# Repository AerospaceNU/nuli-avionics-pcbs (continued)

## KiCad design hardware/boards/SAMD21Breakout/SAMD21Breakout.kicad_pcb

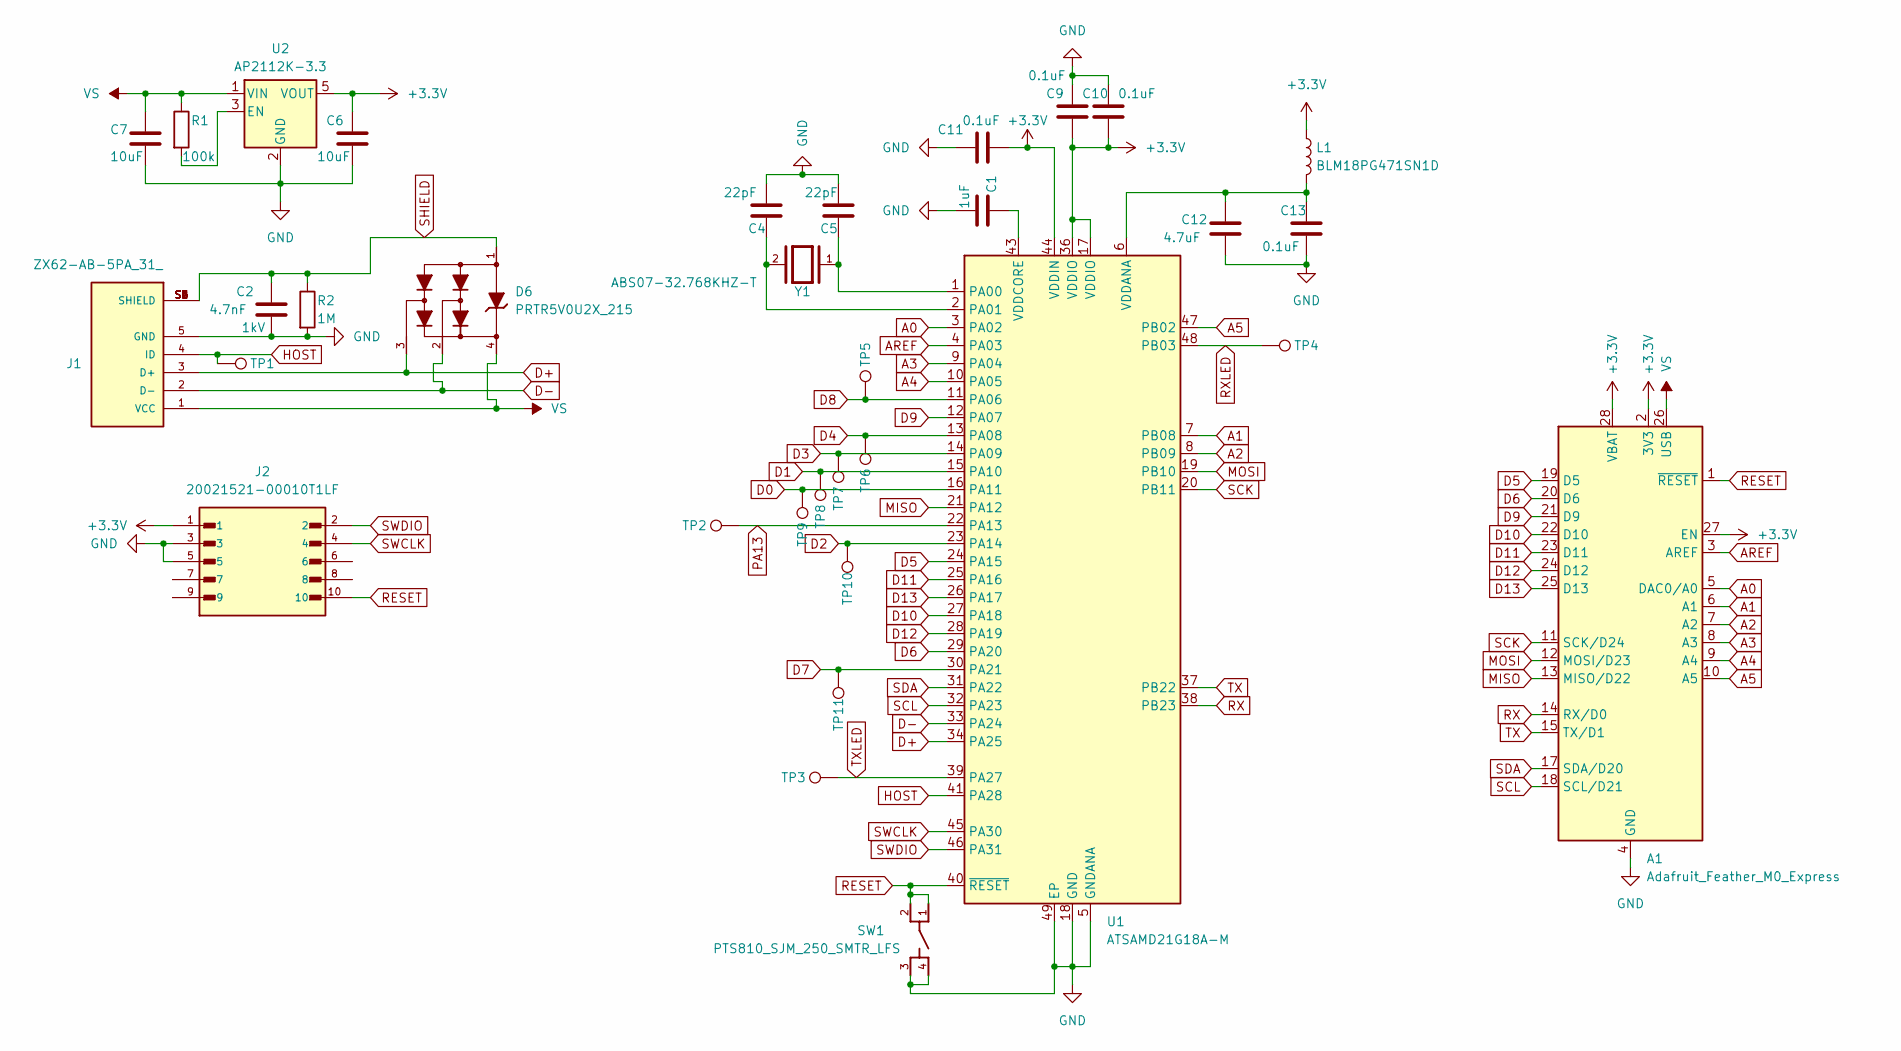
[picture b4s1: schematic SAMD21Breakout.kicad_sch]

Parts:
A1: Adafruit_Feather_M0_Express; Adafruit_Feather
C1: 1uF; C_0603_1608Metric
C2: 4.7nF; C_1206_3216Metric; Voltage 1kV
C4, C5: 22pF; C_0603_1608Metric
C6, C7: 10uF; C_0603_1608Metric
C9, C10, C11, C13: 0.1uF; C_0603_1608Metric
C12: 4.7uF; C_0603_1608Metric
D6: PRTR5V0U2X_215; SOT143B
J1: ZX62-AB-5PA_31_; HIROSE_ZX62-AB-5PA_31_; PARTREV Jan 1, 2022
J2: 20021521-00010T1LF; AMPHENOL_20021521-00010T1LF; PARTREV N
L1: BLM18PG471SN1D; L_0603_1608Metric
R1: 100k; R_0603_1608Metric
R2: 1M; R_0603_1608Metric
SW1: PTS810_SJM_250_SMTR_LFS; SW_PTS810_SJM_250_SMTR_LFS
TP1, TP2, TP3, TP4, TP5, TP6, TP7, TP8, TP9, TP10, TP11: TestPoint; TestPoint_Pad_D1.0mm
U1: ATSAMD21G18A-M; QFN-48-1EP_7x7mm_P0.5mm_EP5.15x5.15mm
U2: AP2112K-3.3; SOT-23-5
Y1: ABS07-32.768KHZ-T; XTAL_ABS07-32.768KHZ-T; PARTREV 08.19.15

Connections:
+3.3V: A1.2 (3V3), A1.27 (EN), A1.28 (VBAT), C6.1, C9.2, C10.2, C11.2, J2.1, L1.1, U1.17 (VDDIO), U1.36 (VDDIO), U1.44 (VDDIN), U2.5 (VOUT)
A0: A1.5 (DAC0/A0), U1.3 (PA02)
A1: A1.6 (A1), U1.7 (PB08)
A2: A1.7 (A2), U1.8 (PB09)
A3: A1.8 (A3), U1.9 (PA04)
A4: A1.9 (A4), U1.10 (PA05)
A5: A1.10 (A5), U1.47 (PB02)
AREF: A1.3 (AREF), U1.4 (PA03)
D0: TP9.1, U1.16 (PA11)
D1: TP8.1, U1.15 (PA10)
D2: TP10.1, U1.23 (PA14)
D3: TP7.1, U1.14 (PA09)
D4: TP6.1, U1.13 (PA08)
D5: A1.19 (D5), U1.24 (PA15)
D6: A1.20 (D6), U1.29 (PA20)
D7: TP11.1, U1.30 (PA21)
D8: TP5.1, U1.11 (PA06)
D9: A1.21 (D9), U1.12 (PA07)
D10: A1.22 (D10), U1.27 (PA18)
D11: A1.23 (D11), U1.25 (PA16)
D12: A1.24 (D12), U1.28 (PA19)
D13: A1.25 (D13), U1.26 (PA17)
D+: D6.3, J1.3 (D+), U1.34 (PA25)
D-: D6.2, J1.2 (D-), U1.33 (PA24)
GND: A1.4 (GND), A1.16 (GND), C1.2, C2.2, C4.2, C5.2, C6.2, C7.2, C9.1, C10.1, C11.1, C12.2, C13.2, J1.5 (GND), J2.3, J2.5, R2.2, SW1.3, SW1.4, U1.5 (GNDANA), U1.18 (GND), U1.35 (GND), U1.42 (GND), U1.49 (EP), U2.2 (GND)
HOST: J1.4 (ID), TP1.1, U1.41 (PA28)
MISO: A1.13 (MISO/D22), U1.21 (PA12)
MOSI: A1.12 (MOSI/D23), U1.19 (PB10)
unnamed: C5.1, U1.1 (PA00), Y1.1
unnamed: C4.1, U1.2 (PA01), Y1.2
unnamed: C12.1, C13.1, L1.2, U1.6 (VDDANA)
unnamed: C1.1, U1.43 (VDDCORE)
unnamed: R1.2, U2.3 (EN)
PA13: TP2.1, U1.22 (PA13)
RESET: A1.1 (~RESET), J2.10, SW1.1, SW1.2, U1.40 (~RESET)
RX: A1.14 (RX/D0), U1.38 (PB23)
RXLED: TP4.1, U1.48 (PB03)
SCK: A1.11 (SCK/D24), U1.20 (PB11)
SCL: A1.18 (SCL/D21), U1.32 (PA23)
SDA: A1.17 (SDA/D20), U1.31 (PA22)
SHIELD: C2.1, D6.1, J1.S1 (SHIELD), J1.S2 (SHIELD), J1.S3 (SHIELD), J1.S4 (SHIELD), J1.S5 (SHIELD), J1.S6 (SHIELD), R2.1
SWCLK: J2.4, U1.45 (PA30)
SWDIO: J2.2, U1.46 (PA31)
TX: A1.15 (TX/D1), U1.37 (PB22)
TXLED: TP3.1, U1.39 (PA27)
VS: A1.26 (USB), C7.1, D6.4, J1.1 (VCC), R1.1, U2.1 (VIN)

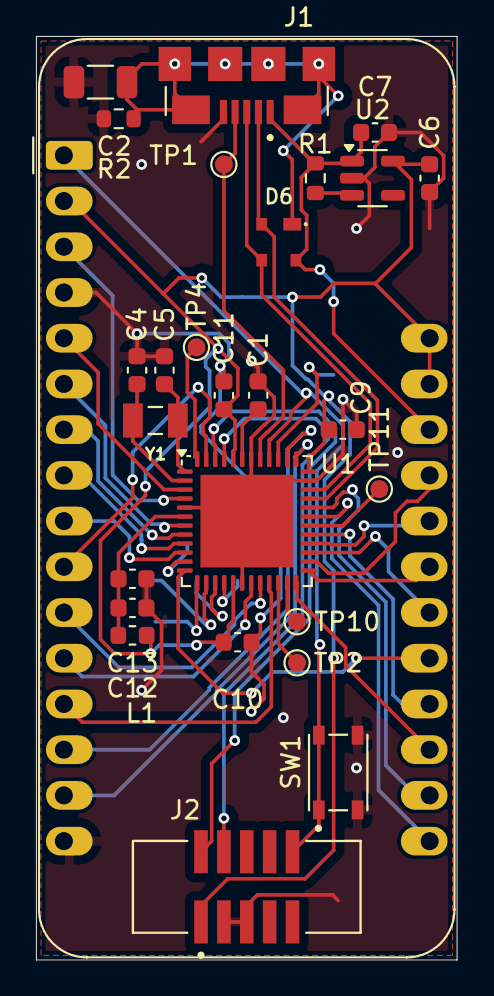
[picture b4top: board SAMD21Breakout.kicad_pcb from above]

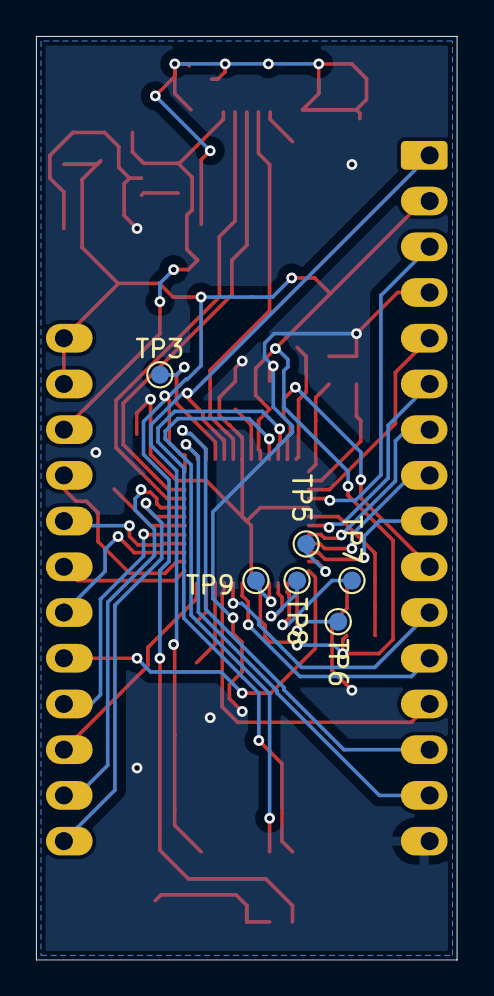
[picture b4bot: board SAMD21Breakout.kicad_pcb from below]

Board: 2 copper layers, 23.4 x 51.3 mm, 33 parts (6 on the bottom side), 46 nets.

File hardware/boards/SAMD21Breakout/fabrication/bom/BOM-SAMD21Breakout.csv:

Comment,Designator,Footprint,LCSC
PRTR5V0U2X_215,D6,SOT143B,C12333
ABS07-32.768KHZ-T,Y1,XTAL_ABS07-32.768KHZ-T,C130253
0.1uF,"C10,C11,C13,C9",C_0603_1608Metric,C14663
1uF,C1,C_0603_1608Metric,C15849
22pF,"C4,C5",C_0603_1608Metric,C1653
4.7uF,C12,C_0603_1608Metric,C19666
10uF,"C6,C7",C_0603_1608Metric,C19702
PTS810_SJM_250_SMTR_LFS,SW1,SW_PTS810_SJM_250_SMTR_LFS,C221895
1M,R2,R_0603_1608Metric,C22935
100k,R1,R_0603_1608Metric,C25803
ZX62-AB-5PA_31_,J1,HIROSE_ZX62-AB-5PA_31_,C2692071
20021521-00010T1LF,J2,AMPHENOL_20021521-00010T1LF,C2972785
AP2112K-3.3,U2,SOT-23-5,C51118
4.7nF,C2,C_1206_3216Metric,C9192
ATSAMD21G18A-M,U1,QFN-48-1EP_7x7mm_P0.5mm_EP5.15x5.15mm,C966903
BLM18PG471SN1D,L1,L_0603_1608Metric,C97853

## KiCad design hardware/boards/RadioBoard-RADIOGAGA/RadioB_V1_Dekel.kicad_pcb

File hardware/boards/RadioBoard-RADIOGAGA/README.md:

# RadioBoard-RADIOGAGA

RadioBoard by Itamar Dekel.

## Contributors

Riley Post, Itamar Dekel

## Status

**Version:** not recorded (the board's title block has no revision)
**Status:** Moved here from CADLab NULIAvionics/RadioBoard-RADIOGAGA; this folder is now the working copy.

## Description

RadioBoard by Itamar Dekel.

- KiCad project: `RadioB_V1_Dekel.kicad_pro`, last saved with KiCad 9.0
- Schematic sheets: `RadioB_V1_Dekel.kicad_sch`, `Connectors.kicad_sch`, `Power.kicad_sch`, `Pinouts.kicad_sch`, `RF Module.kicad_sch`, `untitled.kicad_sch`
- Board size: 60.0 x 22.1 mm
- `fabrication/`: `bom/`, `drill/`, `gerbers/`, `pick-and-place/`

## Manufacturing

- Layers: 6
- Thickness: 1.6 mm
- Surface finish: not set in the board stackup
- Minimum trace/space: 0.15 mm / 0.15 mm (smallest track on the board / default netclass clearance)
- Minimum drill: 0.25 mm (design rule)
- Manufacturer: JLCPCB (the fabrication outputs are JLCPCB's)

## Known Issues

None recorded.

## Revision History

| Version | Date | Changes |
|---|---|---|
| - | 2026-06-11 | Moved into this repo from CADLab NULIAvionics/RadioBoard-RADIOGAGA (history from 2026-04-21 to 2026-06-11 stays there) |

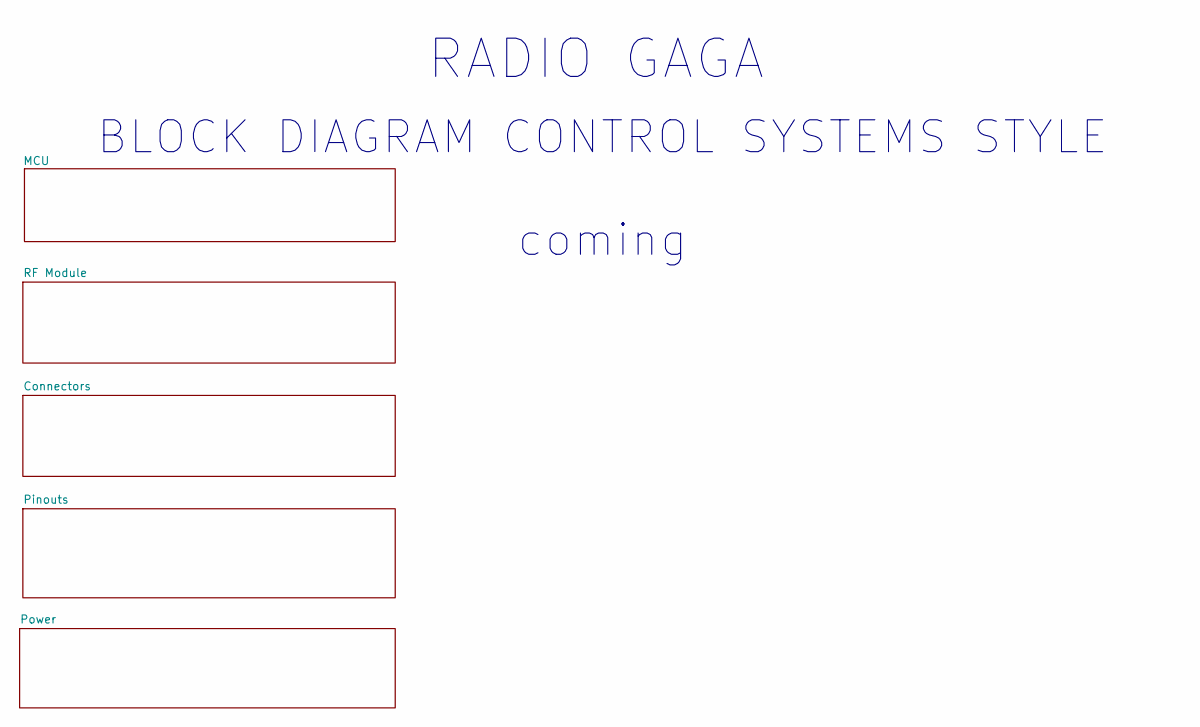
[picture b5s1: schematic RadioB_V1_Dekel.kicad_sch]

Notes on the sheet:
BLOCK DIAGRAM CONTROL SYSTEMS STYLE coming
RADIO GAGA

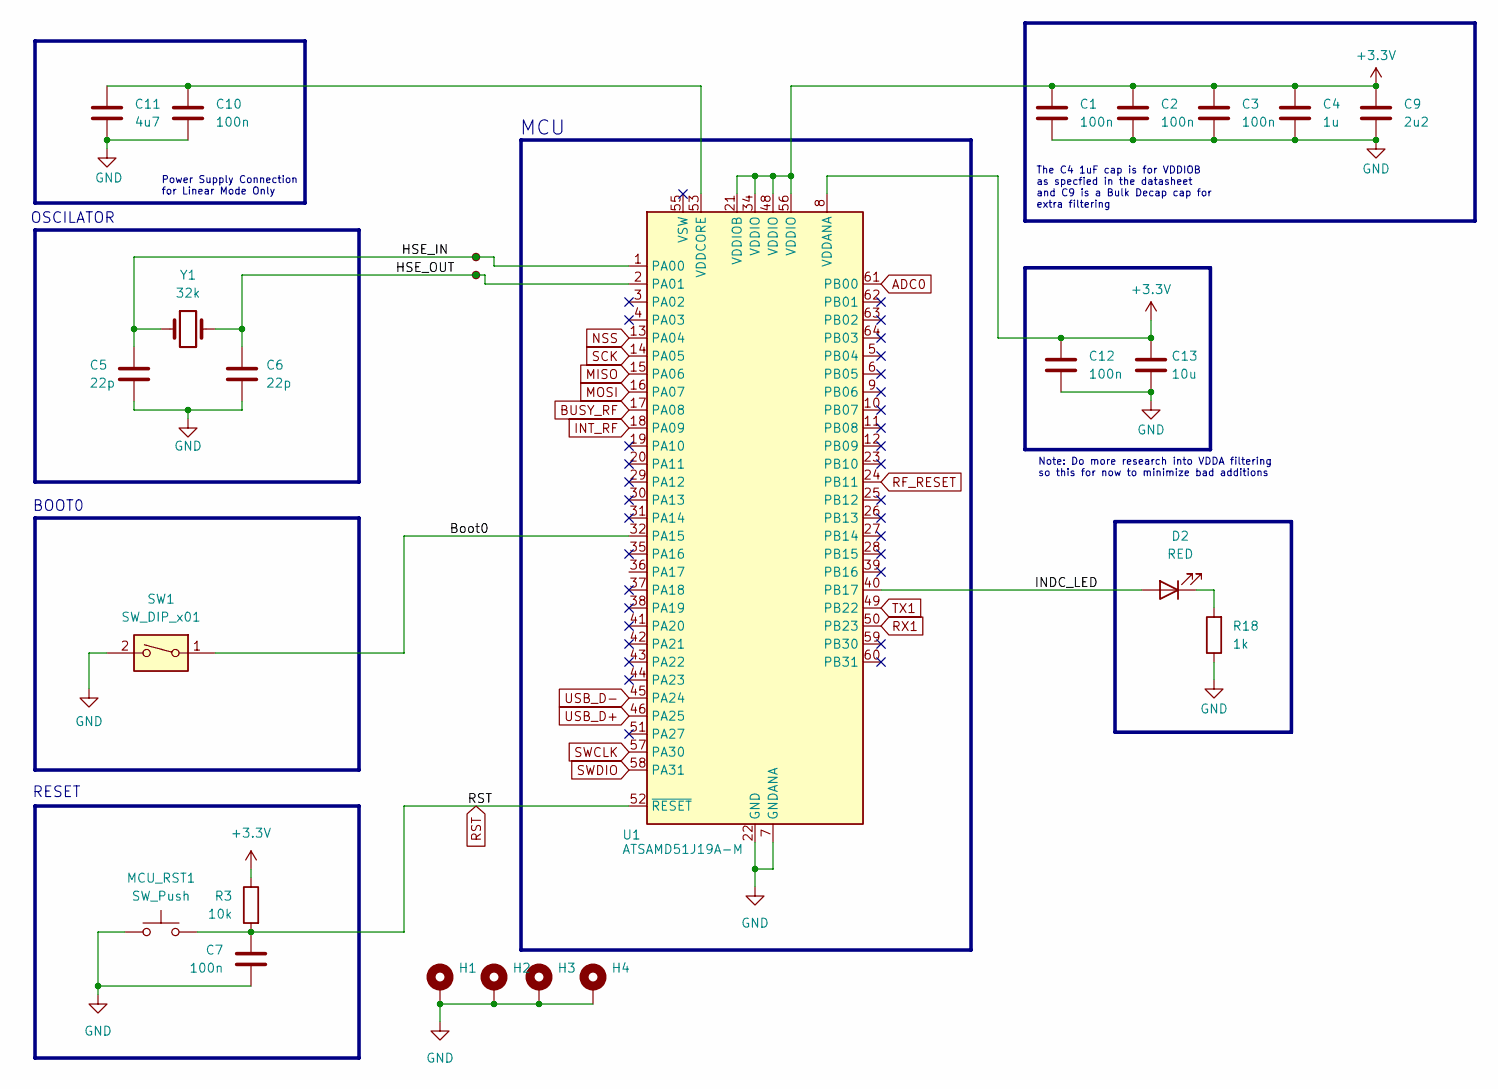
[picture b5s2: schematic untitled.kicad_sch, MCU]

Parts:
C1, C2, C3, C7, C10, C12: 100n; C_0603_1608Metric
C4: 1u; C_0603_1608Metric
C5, C6: 22p; C_0603_1608Metric
C9: 2u2; C_0603_1608Metric
C11: 4u7; C_0603_1608Metric
C13: 10u; C_0603_1608Metric
D2: RED; LED_0805_2012Metric
H1, H2, H3, H4: MountingHole_Pad; MountingHole_2.2mm_M2_Pad_Via
MCU_RST1: SW_Push; SW_F160QG_EWI
R3: 10k; R_0603_1608Metric
R18: 1k; R_0603_1608Metric
SW1: SW_DIP_x01; SW_DIP_SPSTx01_Slide_6.7x4.1mm_W6.73mm_P2.54mm_LowProfile_J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
U1: ATSAMD51J19A-M; QFN-64-1EP_9x9mm_P0.5mm_EP4.7x4.7mm
Y1: 32k; Crystal_SMD_3215-2Pin_3.2x1.5mm
YIN1: TestPoint_Small; TestPoint_Pad_D1.0mm
YOUT1: TestPoint_Small; TestPoint_Pad_D1.0mm

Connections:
+3.3V: C1.1, C2.1, C3.1, C4.1, C9.1, C12.1, C13.1, R3.1, U1.8 (VDDANA), U1.21 (VDDIOB), U1.34 (VDDIO), U1.48 (VDDIO), U1.56 (VDDIO); also elsewhere on the board
/MCU/Boot0: SW1.1, U1.32 (PA15)
/MCU/HSE_IN: C5.1, U1.1 (PA00), Y1.1, YIN1.1
/MCU/HSE_OUT: C6.1, U1.2 (PA01), Y1.2, YOUT1.1
/MCU/INDC_LED: D2.2 (A), U1.40 (PB17)
ADC0: U1.61 (PB00); also elsewhere on the board
BUSY_RF: U1.17 (PA08); also elsewhere on the board
GND: C1.2, C2.2, C3.2, C4.2, C5.2, C6.2, C7.2, C9.2, C10.2, C11.2, C12.2, C13.2, H1.1, H2.1, H3.1, H4.1, MCU_RST1.2, R18.1, SW1.2, U1.7 (GNDANA), U1.22 (GND), U1.33 (GND), U1.47 (GND), U1.54 (GND), U1.65 (GND); also elsewhere on the board
INT_RF: U1.18 (PA09); also elsewhere on the board
MISO: U1.15 (PA06); also elsewhere on the board
MOSI: U1.16 (PA07); also elsewhere on the board
NSS: U1.13 (PA04); also elsewhere on the board
unnamed: D2.1 (K), R18.2
unnamed: C10.1, C11.1, U1.53 (VDDCORE)
RF_RESET: U1.24 (PB11); also elsewhere on the board
RST: C7.1, MCU_RST1.1, R3.2, U1.52 (~RESET); also elsewhere on the board
RX1: U1.50 (PB23); also elsewhere on the board
SCK: U1.14 (PA05); also elsewhere on the board
SWCLK: U1.57 (PA30); also elsewhere on the board
SWDIO: U1.58 (PA31); also elsewhere on the board
TX1: U1.49 (PB22); also elsewhere on the board
USB_D+: U1.46 (PA25); also elsewhere on the board
USB_D-: U1.45 (PA24); also elsewhere on the board

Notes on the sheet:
OSCILATOR
Power Supply Connection for Linear Mode Only
MCU
Note: Do more research into VDDA filtering so this for now to minimize bad additions
The C4 1uF cap is for VDDIOB as specfied in the datasheet and C9 is a Bulk Decap cap for extra filtering
RESET
BOOT0

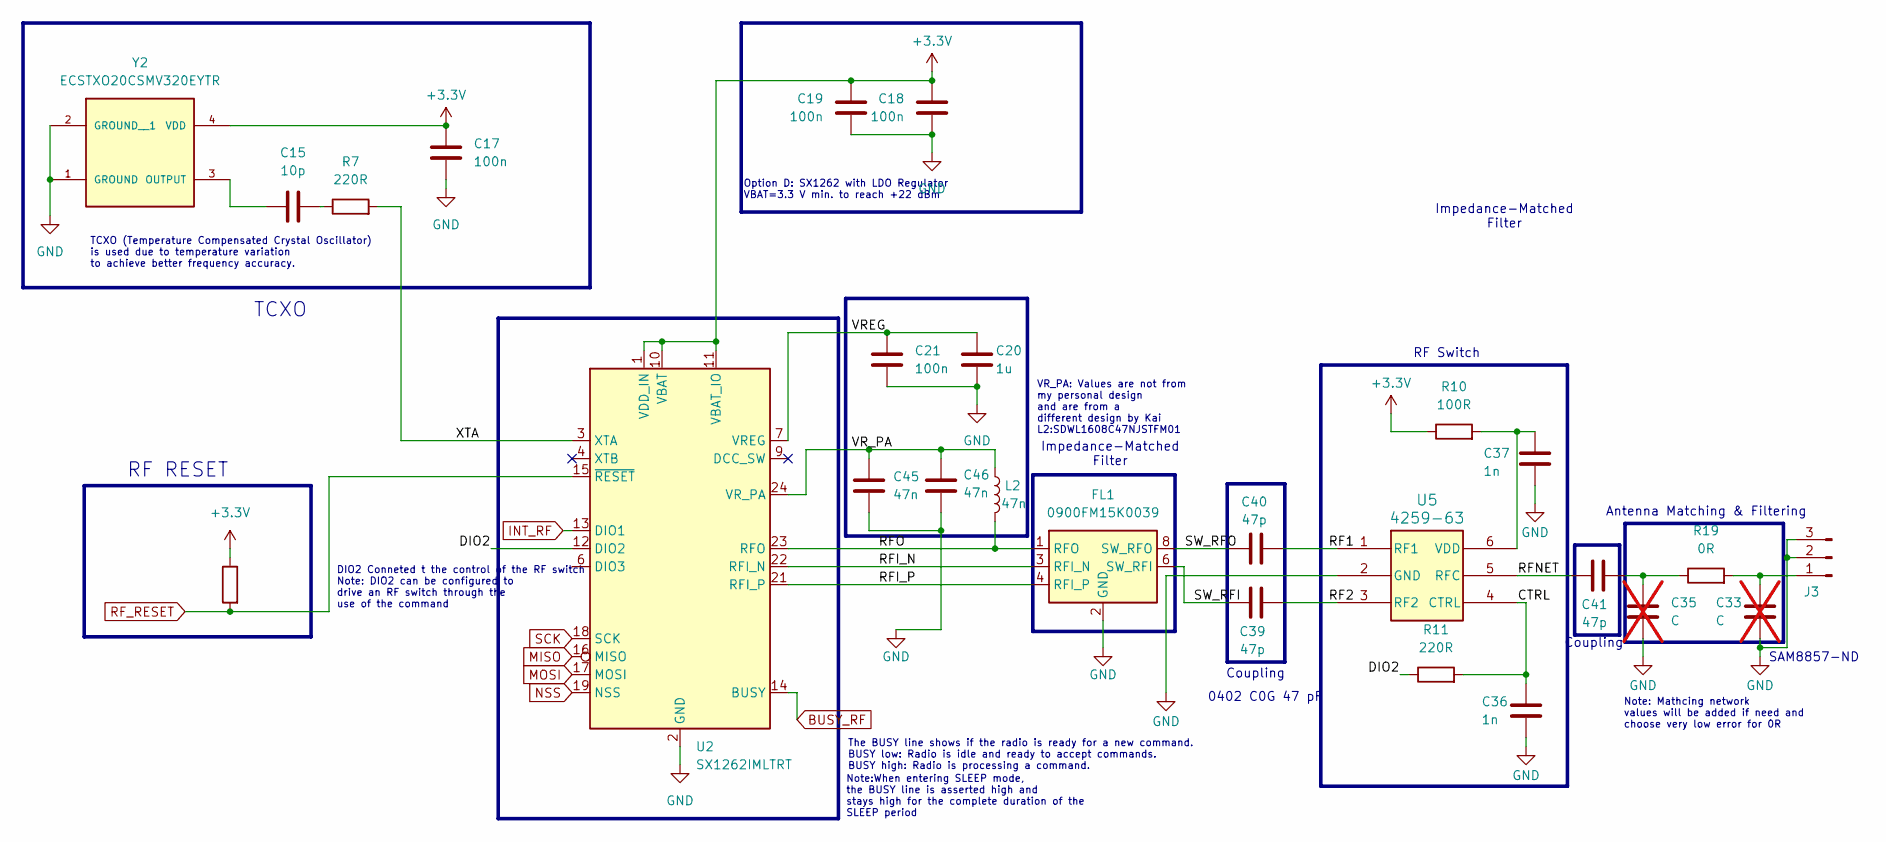
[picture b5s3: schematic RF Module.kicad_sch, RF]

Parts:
C15: 10p; C_0402_1005Metric
C17, C18, C19, C21: 100n; C_0603_1608Metric
C20: 1u; C_0603_1608Metric
C33, C35: C; C_0402_1005Metric; not fitted
C36, C37: 1n; C_0603_1608Metric
C39, C40, C41: 47p; C_0402_1005Metric
C45, C46: 47n; C_0603_1608Metric
FL1: 0900FM15K0039; Balun_Johanson_0900FM15K0039
J3: SMA; CONN_SMA-J-P-H-ST-EM1_SAI
L2: 47n; L_0603_1608Metric
R7: 220R; R_0402_1005Metric
R8: 10k; R_0603_1608Metric
R10: 100R; R_0603_1608Metric
R11: 220R; R_0603_1608Metric
R19: 0R; R_0402_1005Metric
U2: SX1262IMLTRT; QFN-24-1EP_4x4mm_P0.5mm_EP2.6x2.6mm
U5: 4259-63; SC-70-6_PSM-L
Y2: ECSTXO20CSMV320EYTR; OSC_ECSTXO20CSMV320EYTR; PARTREV N/A

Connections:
+3.3V: C17.1, C18.1, C19.1, R8.1, R10.1, U2.1 (VDD_IN), U2.10 (VBAT), U2.11 (VBAT_IO), Y2.4 (VDD); also elsewhere on the board
/RF Module/CTRL: C36.2, R11.2, U5.4 (CTRL)
/RF Module/DIO2: R11.1, U2.12 (DIO2)
/RF Module/RF1: C40.1, U5.1 (RF1)
/RF Module/RF2: C39.1, U5.3 (RF2)
/RF Module/RFI_N: FL1.3 (RFI_N), U2.22 (RFI_N)
/RF Module/RFI_P: FL1.4 (RFI_P), U2.21 (RFI_P)
/RF Module/RFNET: C41.2, U5.5 (RFC)
/RF Module/RFO: FL1.1 (RFO), L2.2, U2.23 (RFO)
/RF Module/SW_RFI: C39.2, FL1.6 (SW_RFI)
/RF Module/SW_RFO: C40.2, FL1.8 (SW_RFO)
/RF Module/VREG: C20.1, C21.1, U2.7 (VREG)
/RF Module/VR_PA: C45.2, C46.2, L2.1, U2.24 (VR_PA)
/RF Module/XTA: R7.2, U2.3 (XTA)
BUSY_RF: U2.14 (BUSY); also elsewhere on the board
GND: C17.2, C18.2, C19.2, C20.2, C21.2, C33.1, C35.1, C36.1, C37.1, C45.1, C46.1, FL1.2 (GND), FL1.5 (GND), FL1.7 (GND), FL1.9 (GND), FL1.10 (GND), J3.2, J3.3, U2.2 (GND), U2.5 (GND), U2.8 (GND), U2.20 (GND), U2.25 (GND), U5.2 (GND), Y2.1 (GROUND), Y2.2 (GROUND__1); also elsewhere on the board
INT_RF: U2.13 (DIO1); also elsewhere on the board
MISO: U2.16 (MISO); also elsewhere on the board
MOSI: U2.17 (MOSI); also elsewhere on the board
NSS: U2.19 (NSS); also elsewhere on the board
unnamed: C15.1, R7.1
unnamed: C35.2, C41.1, R19.1
unnamed: C33.2, J3.1, R19.2
unnamed: C37.2, R10.2, U5.6 (VDD)
unnamed: C15.2, Y2.3 (OUTPUT)
RF_RESET: R8.2, U2.15 (~RESET); also elsewhere on the board
SCK: U2.18 (SCK); also elsewhere on the board

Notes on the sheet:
Coupling
Antenna Matching & Filtering
VR_PA: Values are not from my personal design and are from a different design by Kai L2:SDWL1608C47NJSTFM01
0402 C0G 47 pF
DIO2 Conneted t the control of the RF switch Note: DIO2 can be configured to drive an RF switch through the use of the command
The BUSY line shows if the radio is ready for a new command. BUSY low: Radio is idle and ready to accept commands. BUSY high: Radio is processing a command.
TCXO
Impedance-Matched Filter
TCXO (Temperature Compensated Crystal Oscillator) is used due to temperature variation to achieve better frequency accuracy.
RF Switch
SAM8857-ND
Option D: SX1262 with LDO Regulator VBAT=3.3 V min. to reach +22 dBm
Note:When entering SLEEP mode, the BUSY line is asserted high and stays high for the complete duration of the SLEEP period
Note: Mathcing network values will be added if need and choose very low error for 0R
RF RESET

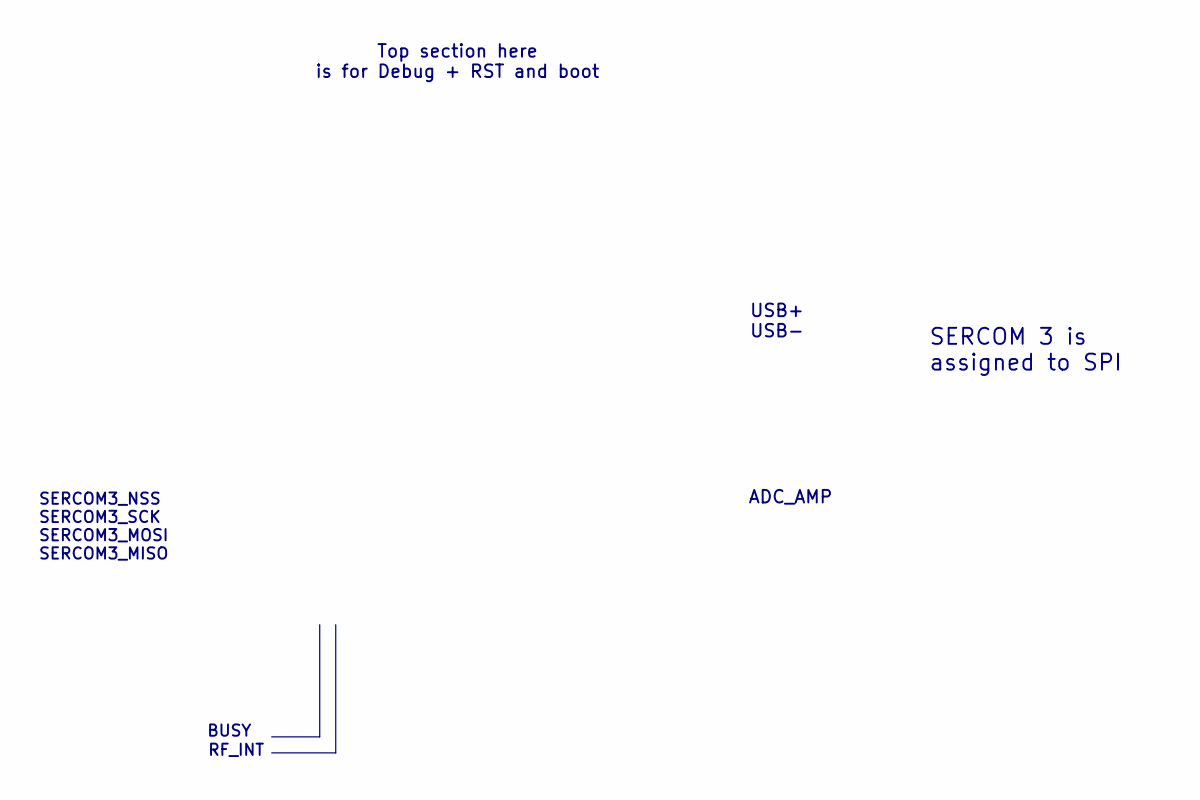
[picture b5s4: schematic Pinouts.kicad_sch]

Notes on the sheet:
RF_INT
Top section here is for Debug + RST and boot
SERCOM3_NSS SERCOM3_SCK SERCOM3_MOSI SERCOM3_MISO
SERCOM 3 is assigned to SPI
BUSY
USB+ USB-
ADC_AMP

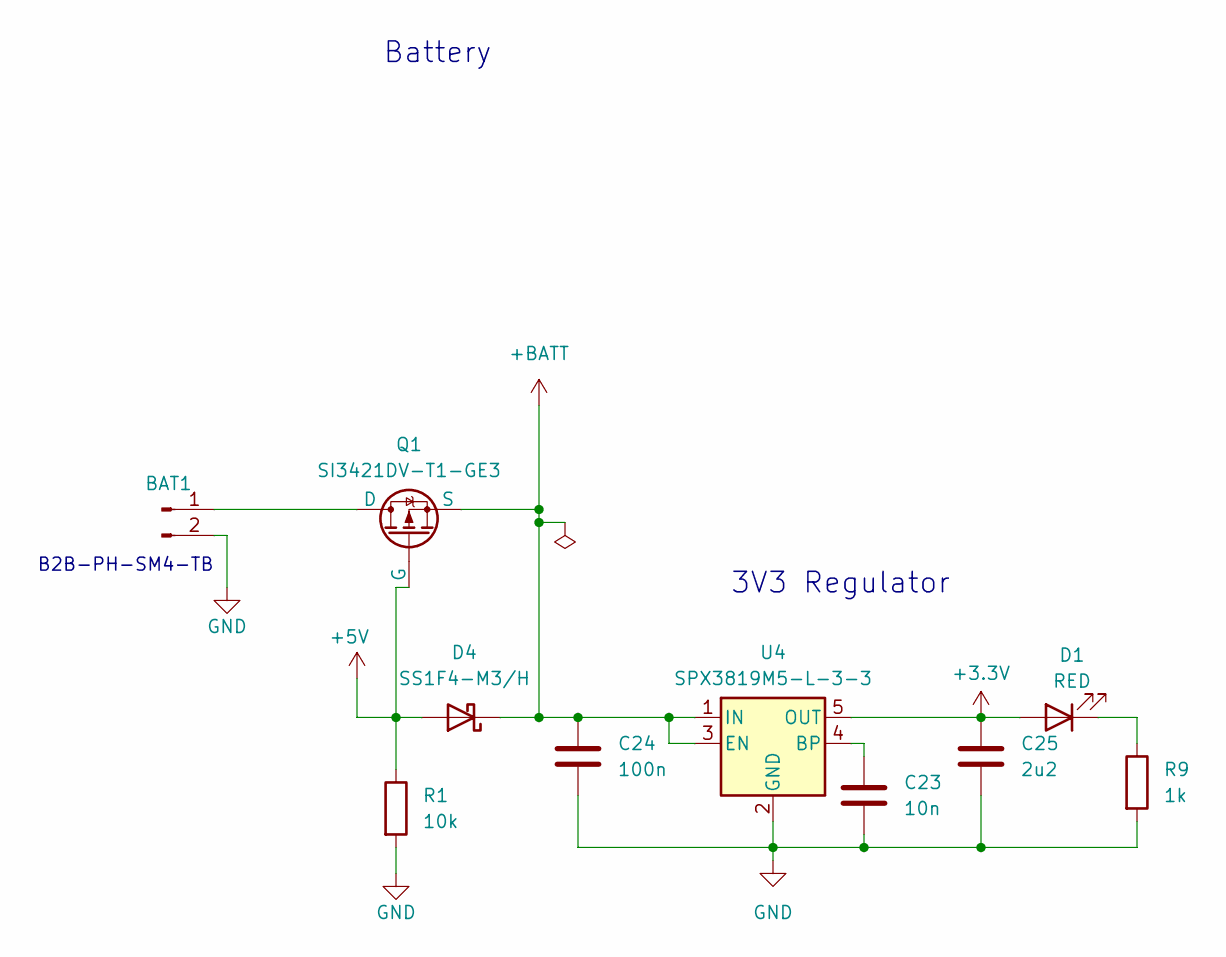
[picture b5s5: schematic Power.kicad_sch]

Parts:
BAT1: Conn_01x02_Pin; JST_PH_B2B-PH-K_1x02_P2.00mm_Vertical
C23: 10n; C_0402_1005Metric
C24: 100n; C_0603_1608Metric
C25: 2u2; C_0603_1608Metric
D1: RED; LED_0805_2012Metric
D4: SS1F4-M3/H; D_SOD-123
Q1: SI3421DV-T1-GE3; TSOP-6_1.65x3.05mm_P0.95mm
R1: 10k; R_0603_1608Metric
R9: 1k; R_0603_1608Metric
U4: SPX3819M5-L-3-3; SOT-23-5

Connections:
+3.3V: C25.1, D1.2 (A), U4.5 (OUT); also elsewhere on the board
+5V: D4.2 (A), Q1.3 (G), R1.1; also elsewhere on the board
+BATT: C24.1, D4.1 (K), Q1.4 (S), U4.1 (IN), U4.3 (EN)
GND: BAT1.2, C23.2, C24.2, C25.2, R1.2, R9.2, U4.2 (GND); also elsewhere on the board
unnamed: BAT1.1, Q1.1 (D), Q1.2 (D), Q1.5 (D), Q1.6 (D)
unnamed: D1.1 (K), R9.1
unnamed: C23.1, U4.4 (BP)

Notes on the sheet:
3V3 Regulator
Battery
B2B-PH-SM4-TB

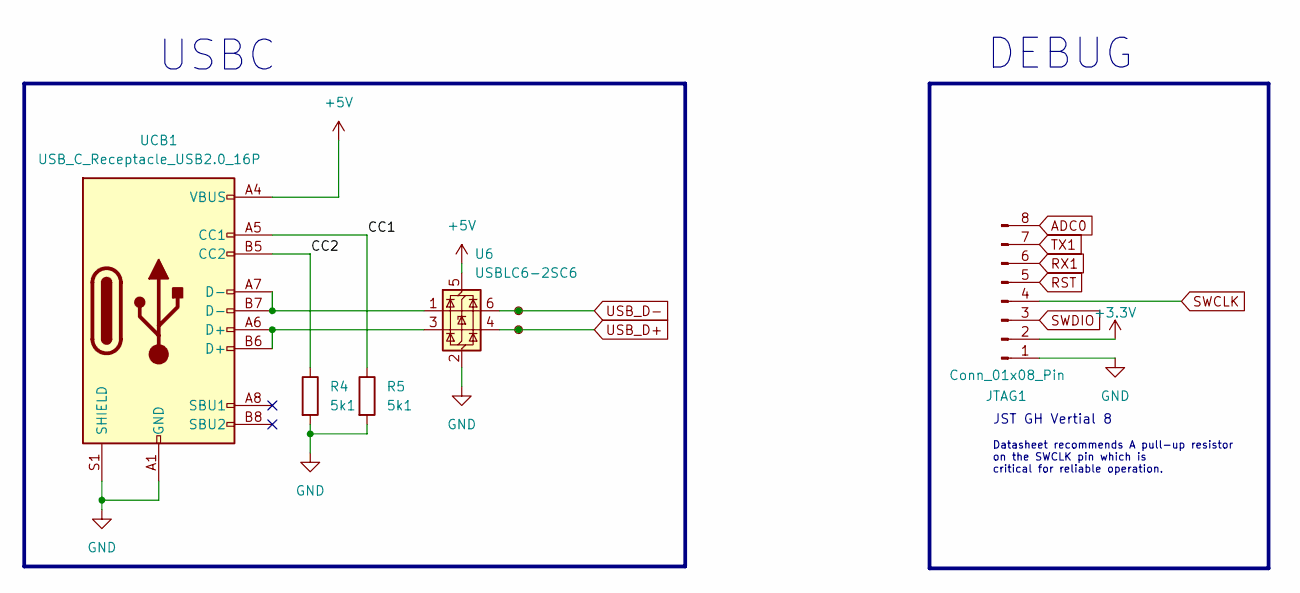
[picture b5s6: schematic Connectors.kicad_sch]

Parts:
D+1: TestPoint_Small; TestPoint_Pad_D1.0mm
D-1: TestPoint_Small; TestPoint_Pad_D1.0mm
JTAG1: Conn_01x08_Pin; JST_GH_BM08B-GHS-TBT_1x08-1MP_P1.25mm_Vertical
R4, R5: 5k1; R_0603_1608Metric
U6: USBLC6-2SC6; SOT-23-6
UCB1: USB_C_Receptacle_USB2.0_16P; USB_C_Receptacle_GCT_USB4105-xx-A_16P_TopMnt_Horizontal

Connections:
+3.3V: JTAG1.2; also elsewhere on the board
+5V: U6.5 (VBUS), UCB1.A4 (VBUS), UCB1.A9 (VBUS), UCB1.B4 (VBUS), UCB1.B9 (VBUS); also elsewhere on the board
/Connectors/CC1: R5.1, UCB1.A5 (CC1)
/Connectors/CC2: R4.1, UCB1.B5 (CC2)
ADC0: JTAG1.8; also elsewhere on the board
GND: JTAG1.1, R4.2, R5.2, U6.2 (GND), UCB1.A1 (GND), UCB1.A12 (GND), UCB1.B1 (GND), UCB1.B12 (GND), UCB1.S1 (SHIELD); also elsewhere on the board
unnamed: U6.1 (I/O1), UCB1.A7 (D-), UCB1.B7 (D-)
unnamed: U6.3 (I/O2), UCB1.A6 (D+), UCB1.B6 (D+)
RST: JTAG1.5; also elsewhere on the board
RX1: JTAG1.6; also elsewhere on the board
SWCLK: JTAG1.4; also elsewhere on the board
SWDIO: JTAG1.3; also elsewhere on the board
TX1: JTAG1.7; also elsewhere on the board
USB_D+: D+1.1, U6.4 (I/O2); also elsewhere on the board
USB_D-: D-1.1, U6.6 (I/O1); also elsewhere on the board

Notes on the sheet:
USBC
Datasheet recommends A pull-up resistor on the SWCLK pin which is critical for reliable operation.
DEBUG
JST GH Vertial 8

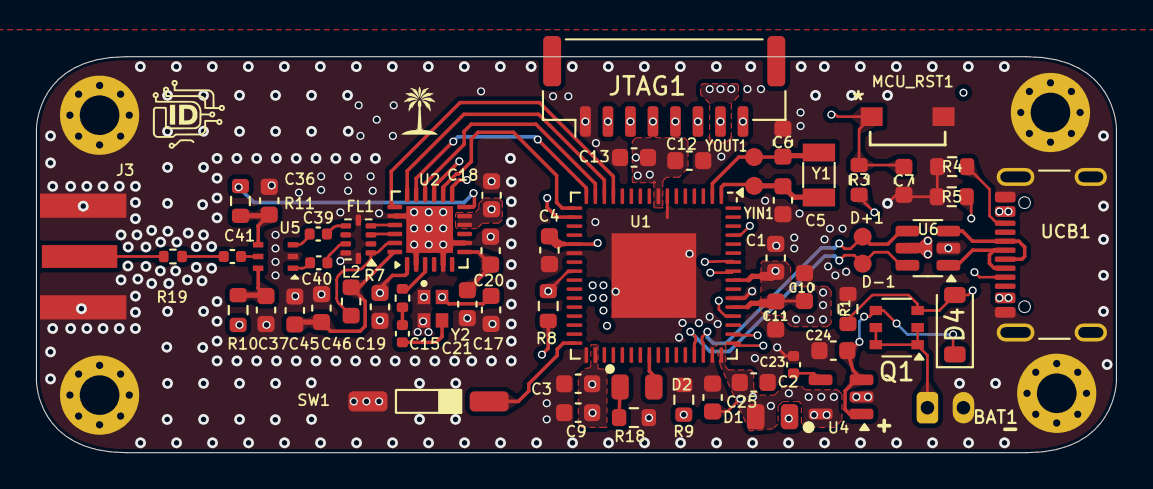
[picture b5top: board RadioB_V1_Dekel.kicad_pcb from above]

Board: 6 copper layers, 60.0 x 22.0 mm, 66 parts (0 on the bottom side), 50 nets.

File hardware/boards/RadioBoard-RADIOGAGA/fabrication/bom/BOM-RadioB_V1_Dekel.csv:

Comment,Designator,Footprint,LCSC,Quantity
SW_DIP_x01,SW1,SW_DIP_SPSTx01_Slide_6.7x4.1mm_W6.73mm_P2.54mm_LowProfile_JPin,,1
10n,C23,C_0402_1005Metric,,1
10k,R8,R_0603_1608Metric,,1
100n,C21,C_0603_1608Metric,,1
RED,D1,LED_0805_2012Metric,,1
10k,R3,R_0603_1608Metric,,1
USB_C_Receptacle_USB2.0_16P,UCB1,USB_C_Receptacle_GCT_USB4105-xx-A_16P_TopMnt_Horizontal,,1
100n,C24,C_0603_1608Metric,,1
0900FM15K0039,FL1,Balun_Johanson_0900FM15K0039,,1
100n,C19,C_0603_1608Metric,,1
SPX3819M5-L-3-3,U4,SOT-23-5,,1
22p,C5,C_0603_1608Metric,,1
22p,C6,C_0603_1608Metric,,1
100n,C1,C_0603_1608Metric,,1
ECSTXO20CSMV320EYTR,Y2,OSC_ECSTXO20CSMV320EYTR,,1
1u,C20,C_0603_1608Metric,,1
32k,Y1,Crystal_SMD_3215-2Pin_3.2x1.5mm,,1
100n,C12,C_0603_1608Metric,,1
2u2,C25,C_0603_1608Metric,,1
RED,D2,LED_0805_2012Metric,,1
SI3421DV-T1-GE3,Q1,TSOP-6_1.65x3.05mm_P0.95mm,,1
SS1F4-M3/H,D4,D_SOD-123,,1
1k,R9,R_0603_1608Metric,,1
TestPoint_Small,YOUT1,TestPoint_Pad_D1.0mm,,1
47p,C40,C_0402_1005Metric,,1
100n,C18,C_0603_1608Metric,,1
TestPoint_Small,YIN1,TestPoint_Pad_D1.0mm,,1
100R,R10,R_0603_1608Metric,,1
47n,L2,L_0603_1608Metric,,1
47n,C46,C_0603_1608Metric,,1
47p,C39,C_0402_1005Metric,,1
1k,R18,R_0603_1608Metric,,1
4u7,C11,C_0603_1608Metric,,1
100n,C3,C_0603_1608Metric,,1
220R,R7,R_0402_1005Metric,,1
100n,C17,C_0603_1608Metric,,1
SW_Push,MCU_RST1,SW_F160QG_EWI,,1
10p,C15,C_0402_1005Metric,,1
SX1262IMLTRT,U2,QFN-24-1EP_4x4mm_P0.5mm_EP2.6x2.6mm,,1
1u,C4,C_0603_1608Metric,,1
4259-63,U5,SC-70-6_PSM-L,,1
5k1,R5,R_0603_1608Metric,,1
0R,R19,R_0402_1005Metric,,1
47p,C41,C_0402_1005Metric,,1
Conn_01x08_Pin,JTAG1,JST_GH_BM08B-GHS-TBT_1x08-1MP_P1.25mm_Vertical,,1
5k1,R4,R_0603_1608Metric,,1
10u,C13,C_0603_1608Metric,,1
ATSAMD51J19A-M,U1,QFN-64-1EP_9x9mm_P0.5mm_EP4.7x4.7mm,,1
1n,C36,C_0603_1608Metric,,1
1n,C37,C_0603_1608Metric,,1
Conn_01x02_Pin,BAT1,JST_PH_B2B-PH-K_1x02_P2.00mm_Vertical,,1
SMA,J3,CONN_SMA-J-P-H-ST-EM1_SAI,,1
220R,R11,R_0603_1608Metric,,1
100n,C2,C_0603_1608Metric,,1
USBLC6-2SC6,U6,SOT-23-6,,1
10k,R1,R_0603_1608Metric,,1
100n,C7,C_0603_1608Metric,,1
2u2,C9,C_0603_1608Metric,,1
100n,C10,C_0603_1608Metric,,1
47n,C45,C_0603_1608Metric,,1
